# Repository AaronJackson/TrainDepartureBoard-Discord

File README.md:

# Discord on a Train Departure Board

Still a work in progress.

https://wiki.nottinghack.org.uk/wiki/Train_Station_Display

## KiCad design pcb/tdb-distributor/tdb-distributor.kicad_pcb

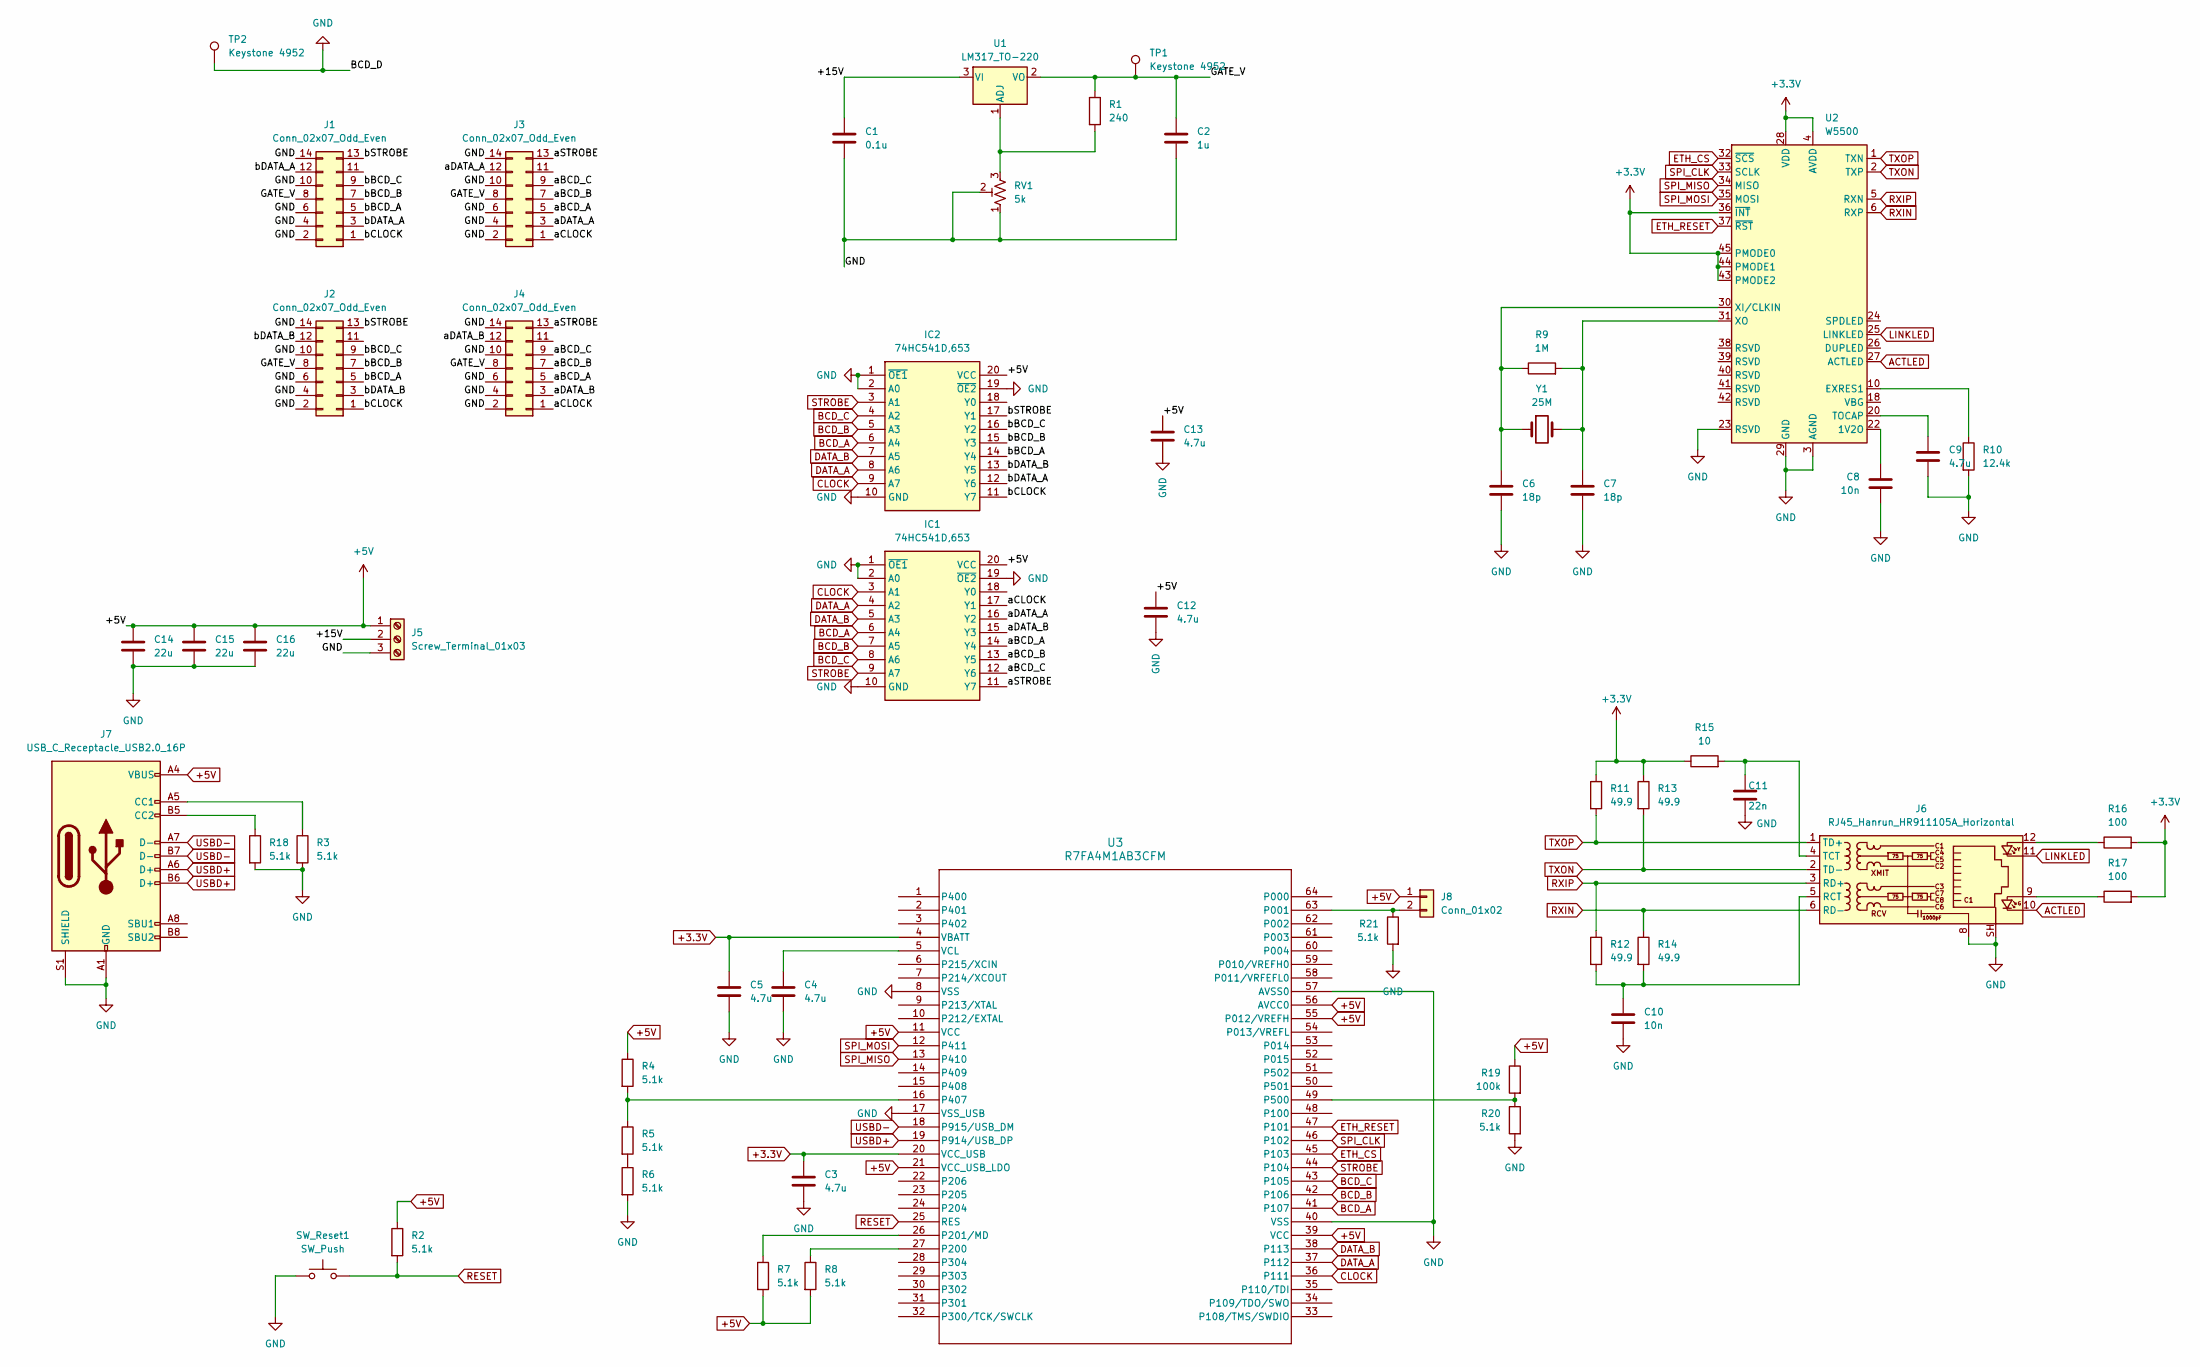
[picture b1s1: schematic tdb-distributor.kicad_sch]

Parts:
C1: 0.1u; C_0603_1608Metric
C2: 1u; C_0603_1608Metric
C3, C4, C5, C9, C12, C13: 4.7u; C_0603_1608Metric
C6, C7: 18p; C_0603_1608Metric
C8, C10: 10n; C_0603_1608Metric
C11: 22n; C_0603_1608Metric
C14, C15, C16: 22u; C_0603_1608Metric
IC1, IC2: 74HC541D,653; SOIC-20W_7.5x12.8mm_P1.27mm; Manufacturer_Part_Number 74HC541D,653
J1, J2, J3, J4: Conn_02x07_Odd_Even; IDC-Header_2x07_P2.54mm_Vertical
J5: Screw_Terminal_01x03; TerminalBlock_WAGO_236-103_1x03_P5.00mm_45Degree
J6: RJ45_Hanrun_HR911105A_Horizontal
J7: USB_C_Receptacle_USB2.0_16P; USB_C_Receptacle_G-Switch_GT-USB-7010ASV
J8: Conn_01x02; PinHeader_1x02_P2.54mm_Vertical
R1: 240; R_0603_1608Metric
R2, R3, R4, R5, R6, R7, R8, R18, R20, R21: 5.1k; R_0603_1608Metric
R9: 1M; R_0603_1608Metric
R10: 12.4k; R_0603_1608Metric
R11, R12, R13, R14: 49.9; R_0603_1608Metric
R15: 10; R_0603_1608Metric
R16, R17: 100; R_0603_1608Metric
R19: 100k; R_0603_1608Metric
RV1: 5k; Potentiometer_Runtron_RM-065_Vertical
SW_Reset1: SW_Push; SW_TH_Tactile_Omron_B3F-10xx
TP1, TP2: Keystone 4952; TestPoint_THTPad_2.5x2.5mm_Drill1.2mm
U1: LM317_TO-220; TO-220-3_Vertical
U2: W5500; LQFP-48_7x7mm_P0.5mm
U3: R7FA4M1AB3CFM; PLQP0064KB-C_REN
Y1: 25M; Crystal_SMD_5032-2Pin_5.0x3.2mm

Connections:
+3.3V: C3.1, C5.1, R11.1, R13.1, R15.1, R16.2, R17.2, U2.4 (AVDD), U2.8 (AVDD), U2.11 (AVDD), U2.15 (AVDD), U2.17 (AVDD), U2.21 (AVDD), U2.28 (VDD), U2.36 (~INT), U2.43 (PMODE2), U2.44 (PMODE1), U2.45 (PMODE0), U3.4 (VBATT), U3.20 (VCC_USB)
+5V: C12.1, C13.1, C14.1, C15.1, C16.1, IC1.20 (VCC), IC2.20 (VCC), J5.1, J7.A4 (VBUS), J7.A9 (VBUS), J7.B4 (VBUS), J7.B9 (VBUS), J8.1, R2.1, R4.1, R7.2, R8.2, R19.1, U3.11 (VCC), U3.21 (VCC_USB_LDO), U3.39 (VCC), U3.55 (P012/VREFH), U3.56 (AVCC0)
/+15V: C1.1, J5.2, U1.3 (VI)
/GATE_V: C2.1, J1.8, J2.8, J3.8, J4.8, R1.1, TP1.1, U1.2 (VO)
/aBCD_A: IC1.14 (Y4), J3.5, J4.5
/aBCD_B: IC1.13 (Y5), J3.7, J4.7
/aBCD_C: IC1.12 (Y6), J3.9, J4.9
/aCLOCK: IC1.17 (Y1), J3.1, J4.1
/aDATA_A: IC1.16 (Y2), J3.3, J3.12
/aDATA_B: IC1.15 (Y3), J4.3, J4.12
/aSTROBE: IC1.11 (Y7), J3.13, J4.13
/bBCD_A: IC2.14 (Y4), J1.5, J2.5
/bBCD_B: IC2.15 (Y3), J1.7, J2.7
/bBCD_C: IC2.16 (Y2), J1.9, J2.9
/bCLOCK: IC2.11 (Y7), J1.1, J2.1
/bDATA_A: IC2.12 (Y6), J1.3, J1.12
/bDATA_B: IC2.13 (Y5), J2.3, J2.12
/bSTROBE: IC2.17 (Y1), J1.13, J2.13
ACTLED: J6.10, U2.27 (ACTLED)
BCD_A: IC1.6 (A4), IC2.6 (A4), U3.41 (P107)
BCD_B: IC1.7 (A5), IC2.5 (A3), U3.42 (P106)
BCD_C: IC1.8 (A6), IC2.4 (A2), U3.43 (P105)
CLOCK: IC1.3 (A1), IC2.9 (A7), U3.36 (P111)
DATA_A: IC1.4 (A2), IC2.8 (A6), U3.37 (P112)
DATA_B: IC1.5 (A3), IC2.7 (A5), U3.38 (P113)
ETH_CS: U2.32 (~SCS), U3.45 (P103)
ETH_RESET: U2.37 (~RST), U3.47 (P101)
GND: C1.2, C2.2, C3.2, C4.2, C5.2, C6.2, C7.2, C8.2, C9.2, C10.1, C11.2, C12.2, C13.2, C14.2, C15.2, C16.2, IC1.1 (~OE1), IC1.2 (A0), IC1.10 (GND), IC1.19 (~OE2), IC2.1 (~OE1), IC2.2 (A0), IC2.10 (GND), IC2.19 (~OE2), J1.2, J1.4, J1.6, J1.10, J1.14, J2.2, J2.4, J2.6, J2.10, J2.14, J3.2, J3.4, J3.6, J3.10, J3.14, J4.2, J4.4, J4.6, J4.10, J4.14, J5.3, J6.8, J6.SH, J7.A1 (GND), J7.A12 (GND), J7.B1 (GND), J7.B12 (GND), J7.S1 (SHIELD), R3.2, R6.2, R10.2, R18.2, R20.2, R21.2, RV1.1, RV1.2, SW_Reset1.1, TP2.1, U2.3 (AGND), U2.9 (AGND), U2.14 (AGND), U2.16 (AGND), U2.19 (AGND), U2.23 (RSVD), U2.29 (GND), U2.48 (AGND), U3.8 (VSS), U3.17 (VSS_USB), U3.40 (VSS), U3.57 (AVSS0)
LINKLED: J6.11, U2.25 (LINKLED)
unnamed: J6.9, R17.1
unnamed: J6.12, R16.1
unnamed: C10.2, J6.5 (RCT), R12.2, R14.2
unnamed: C11.1, J6.4 (TCT), R15.2
unnamed: J7.A5 (CC1), R3.1
unnamed: J7.B5 (CC2), R18.1
unnamed: J8.2, R21.1, U3.63 (P001)
unnamed: R5.2, R6.1
unnamed: R1.2, RV1.3, U1.1 (ADJ)
unnamed: C8.1, U2.22 (1V2O)
unnamed: R10.1, U2.10 (EXRES1)
unnamed: C9.1, U2.20 (TOCAP)
unnamed: C6.1, R9.1, U2.30 (XI/CLKIN), Y1.1
unnamed: C7.1, R9.2, U2.31 (XO), Y1.2
unnamed: R8.1, U3.27 (P200)
unnamed: R7.1, U3.26 (P201/MD)
unnamed: R4.2, R5.1, U3.16 (P407)
unnamed: R19.2, R20.1, U3.49 (P500)
unnamed: C4.1, U3.5 (VCL)
RESET: R2.2, SW_Reset1.2, U3.25 (RES)
RXIN: J6.6 (RD-), R14.1, U2.6 (RXP)
RXIP: J6.3 (RD+), R12.1, U2.5 (RXN)
SPI_CLK: U2.33 (SCLK), U3.46 (P102)
SPI_MISO: U2.34 (MISO), U3.13 (P410)
SPI_MOSI: U2.35 (MOSI), U3.12 (P411)
STROBE: IC1.9 (A7), IC2.3 (A1), U3.44 (P104)
TXON: J6.2 (TD-), R13.2, U2.2 (TXP)
TXOP: J6.1 (TD+), R11.2, U2.1 (TXN)
USBD+: J7.A6 (D+), J7.B6 (D+), U3.19 (P914/USB_DP)
USBD-: J7.A7 (D-), J7.B7 (D-), U3.18 (P915/USB_DM)

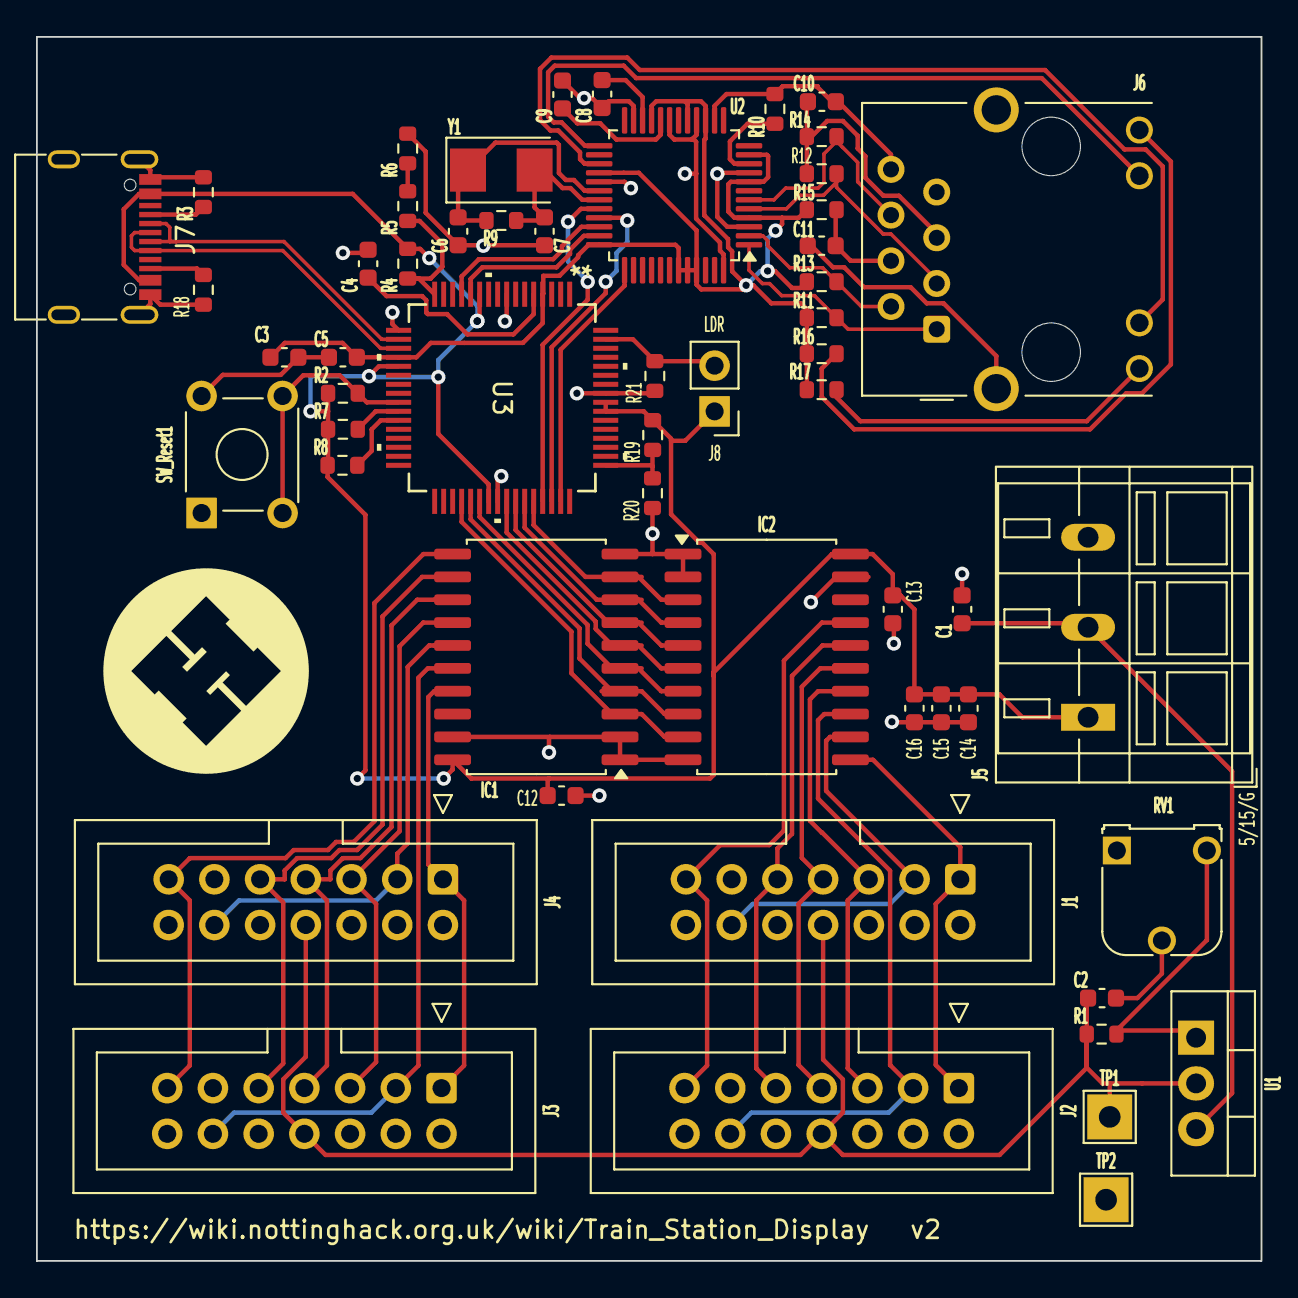
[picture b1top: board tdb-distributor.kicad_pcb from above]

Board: 2 copper layers, 68.0 x 68.0 mm, 55 parts (0 on the bottom side), 59 nets.

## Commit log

2024-02-11 It shows text!
2024-02-12 Clean up and some comments
2024-02-14 Version 1 of PCB
2024-02-14 Cleaned up version of code
2024-02-14 Add labels to power input
2024-02-15 Local project settings
2024-02-15 kicad gitignore
2024-03-02 Fully working! Optimisation required
2024-03-02 Replace delayMicroseconds(1) with three NOPs
2024-03-02 delay between rows not required when latching is of sufficient duration
2024-03-02 Raw buffer access to avoid rotation and index checking
2024-03-02 Split inner bit banging loop to avoid modulo
2024-03-02 Cleanup intermittent mqtt polling
2024-03-02 Query NTP for time every 10 minutes
2024-03-03 Remove unnecessary comparison
2024-03-03 Clean up a few things
2024-03-17 Switch to interrupt driven drawing
    This change is pretty disgusting but an interrupt > 50uS is likely to
    cause the WiFi or TCP connection to drop. I think this is due to the
    WiFi connection on an Uno R4 being driven over UART, which itself
    requires interrupts. Anyway, breaking this into smaller segments seems
    to avoid it crashing, and still allows for a framerate of > 150fps,
    without the occasionally blip caused by mqtt.loop().
2024-03-17 Notify on restart
2024-03-17 Slow down the text scrolling slightly
2024-03-18 Add additional NOPs to PULSE
    This is required now that it's being drawn from an ISR. Presumably
    UART / WiFi interrupts were frequent enough to slow the drawBuffer
    routine down enough.
2024-03-18 Slow down the drawBufferISR timer
2024-03-18 Improve drawing now that we are using an ISR
2024-03-18 Comment about drawBufferISR and why it's disgusting
2024-12-19 licence
2024-12-19 replace org readme with markdown
2024-12-19 Board redesign
    Includes R7 MPU and WizNet
    Adds buffer chips to hopefully support both sides of the display
2024-12-19 minor drc cleanup
2024-12-21 Update pinout to reflect PCB v2
2025-01-01 Changes for board v2
